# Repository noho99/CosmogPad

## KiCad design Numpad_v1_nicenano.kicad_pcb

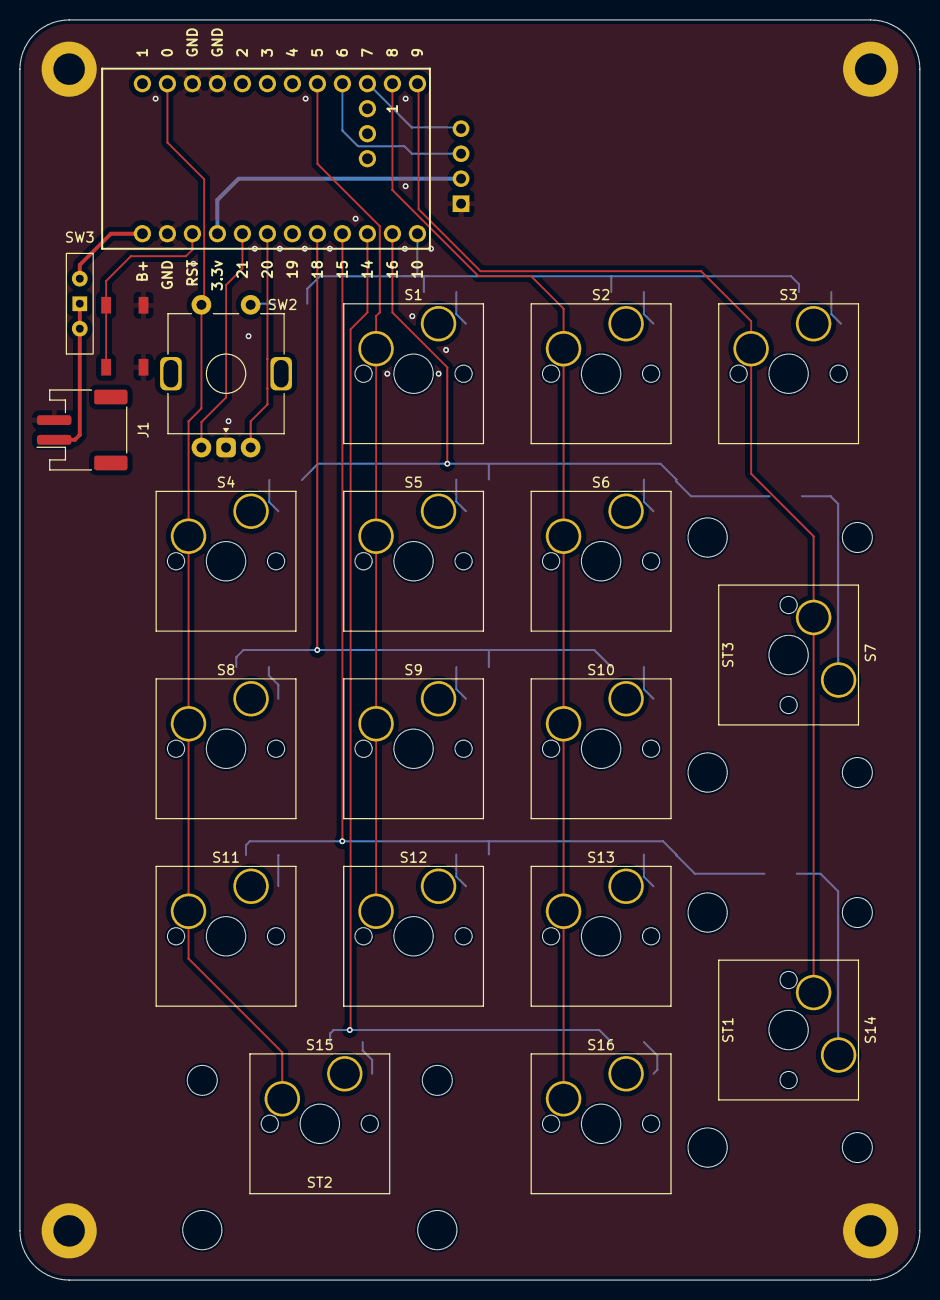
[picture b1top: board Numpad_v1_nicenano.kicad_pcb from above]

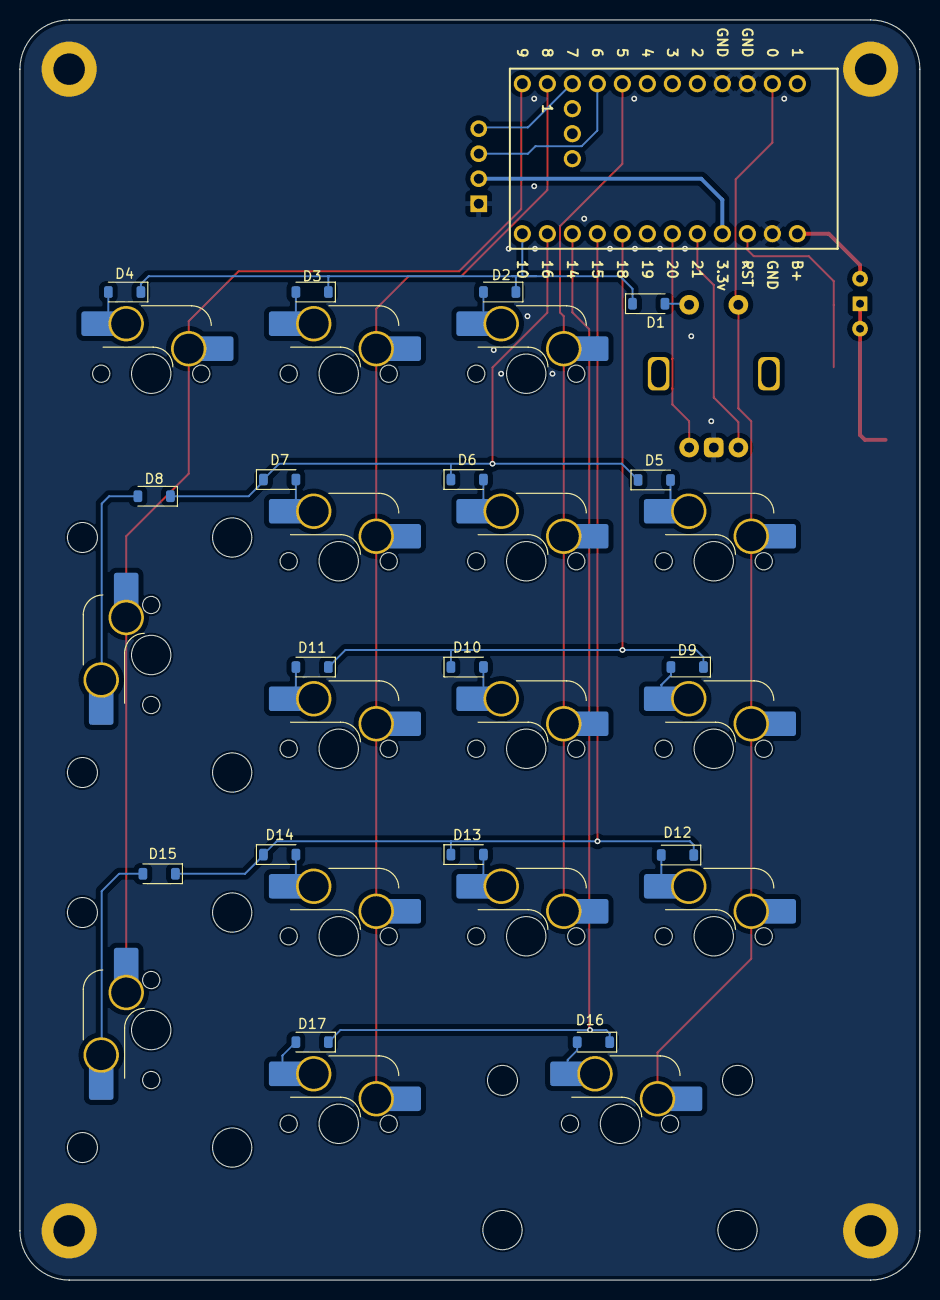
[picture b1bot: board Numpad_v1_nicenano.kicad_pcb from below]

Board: 2 copper layers, 91.4 x 128.0 mm, 46 parts (18 on the bottom side), 35 nets.

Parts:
D1, D2, D3, D4, D5, D6, D7, D8, D9, D10, D11, D12, D13, D14, D15, D16, D17: Diode; D_SOD-123
H1, H2, H3, H4: MountingHole_Pad; MountingHole_3.2mm_M3_DIN965_Pad
J1: Conn_01x02_Socket; JST_PH_S2B-PH-SM4-TB_1x02-1MP_P2.00mm_Horizontal
J2: OLED_128x32
S1, S2, S3, S4, S5, S6, S8, S9, S10, S11, S12, S13, S16: Keyswitch; SW_Hotswap_Kailh_MX_Plated_1.00u
S7, S14, S15: Keyswitch; SW_Hotswap_Kailh_MX_Plated_2.00u
ST1, ST2, ST3: MX_stab_2; Stabilizer_Cherry_MX_2.00u
SW1: SW_DPST_x2; Button_TL3342
SW2: RotaryEncoder_Switch; ROT_Alps_EC11E-Switch
SW3: SW_Wuerth_450301014042; SW_Slide-03_Wuerth-WS-SLTV_10x2.5x6.4_P2.54mm
U1: Nice_Nano_V2

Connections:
3.3V: J2.2 (VCC), U1.21 (3.3v)
3.7V: J1.1, SW3.1 (B), SW3.2 (C)
B+: SW3.3 (A), U1.24 (B+)
Col 1: S4.1, S8.1, S11.1, S15.1, SW2.S2, U1.2 (0)
Col 2: S1.1, S5.1, S9.1, S12.1, U1.8 (5)
Col 3: S2.1, S6.1, S10.1, S13.1, S16.1, U1.11 (8)
Col 4: S3.1, S7.1, S14.1, U1.12 (9)
GND: H1.1, H2.1, H3.1, H4.1, J1.2, J2.1 (GND), SW1.2 (B), SW2.C, U1.3 (GND), U1.4 (GND), U1.23 (GND)
unnamed: D2.2 (A), S1.2
unnamed: D3.2 (A), S2.2
unnamed: D4.2 (A), S3.2
unnamed: D5.2 (A), S4.2
unnamed: D6.2 (A), S5.2
unnamed: D7.2 (A), S6.2
unnamed: D8.2 (A), S7.2
unnamed: D9.2 (A), S8.2
unnamed: D10.2 (A), S9.2
unnamed: D11.2 (A), S10.2
unnamed: D12.2 (A), S11.2
unnamed: D13.2 (A), S12.2
unnamed: D14.2 (A), S13.2
unnamed: D15.2 (A), S14.2
unnamed: D16.2 (A), S15.2
unnamed: D17.2 (A), S16.2
RST: SW1.1 (A), U1.22 (RST)
Rot_A: SW2.A, U1.20 (21)
Rot_B: SW2.B, U1.19 (20)
Rot_S1: D1.2 (A), SW2.S1
Row 1: D1.1 (K), D2.1 (K), D3.1 (K), D4.1 (K), U1.13 (10)
Row 2: D5.1 (K), D6.1 (K), D7.1 (K), D8.1 (K), U1.14 (16)
Row 3: D9.1 (K), D10.1 (K), D11.1 (K), U1.17 (18)
Row 4: D12.1 (K), D13.1 (K), D14.1 (K), D15.1 (K), U1.16 (15)
Row 5: D16.1 (K), D17.1 (K), U1.15 (14)
SCL: J2.3 (SCL), U1.9 (6)
SDA: J2.4 (SDA), U1.10 (7)

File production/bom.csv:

Designator,Footprint,Quantity,Value,LCSC Part #
"D1, D10, D11, D12, D13, D14, D15, D16, D17, D2, D3, D4, D5, D6, D7, D8, D9",D_SOD-123,17,Diode,
J1,JST_PH_S2B-PH-SM4-TB_1x02-1MP_P2.00mm_Horizontal,1,Conn_01x02_Socket,
J2,OLED_128x32,1,OLED_128x32,
"S1, S10, S11, S12, S13, S16, S2, S3, S4, S5, S6, S8, S9",SW_Hotswap_Kailh_MX_Plated_1.00u,13,Keyswitch,
"S14, S15, S7",SW_Hotswap_Kailh_MX_Plated_2.00u,3,Keyswitch,
"ST1, ST2, ST3",Stabilizer_Cherry_MX_2.00u,3,MX_stab_2,
SW1,Button_TL3342,1,SW_DPST_x2,
SW2,ROT_Alps_EC11E-Switch,1,RotaryEncoder_Switch,
SW3,SW_Slide-03_Wuerth-WS-SLTV_10x2.5x6.4_P2.54mm,1,SW_Wuerth_450301014042,
U1,Nice_Nano_V2,1,Nice_Nano_V2,

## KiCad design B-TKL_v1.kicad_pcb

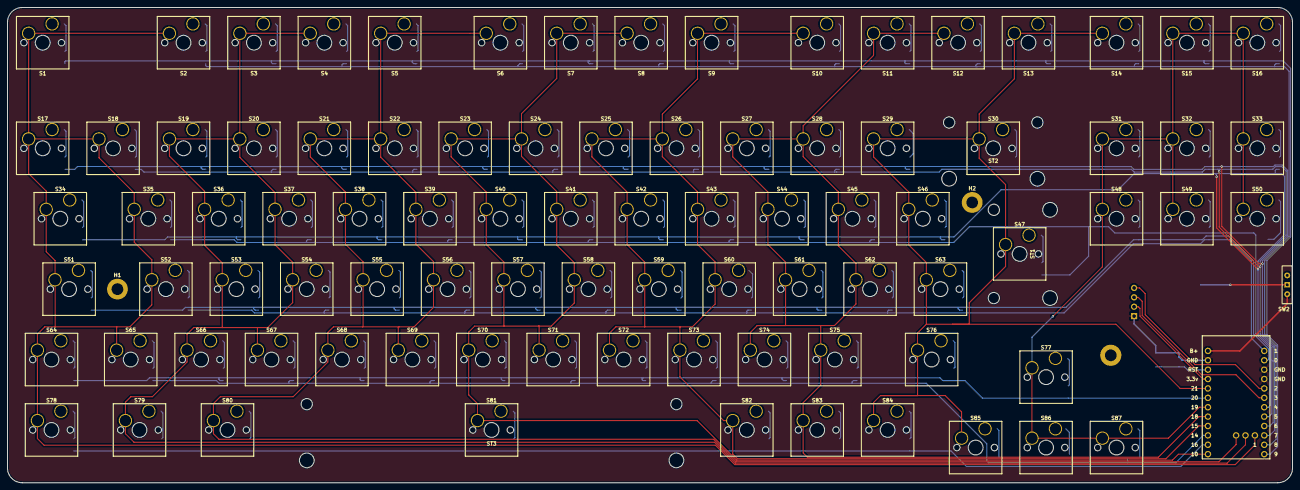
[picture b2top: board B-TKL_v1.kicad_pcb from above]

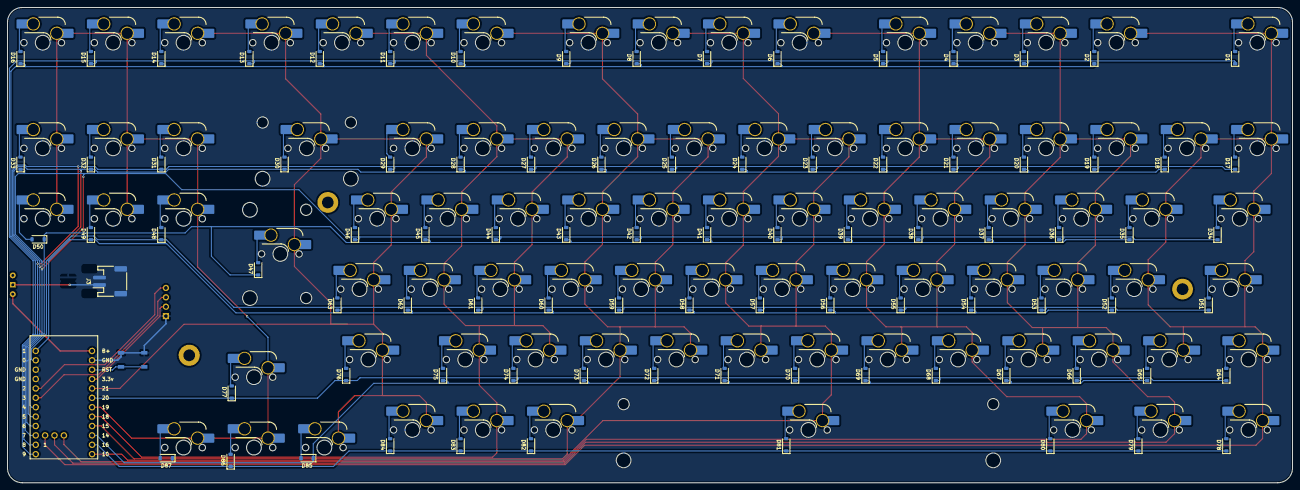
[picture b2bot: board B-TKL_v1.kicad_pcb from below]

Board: 2 copper layers, 347.7 x 128.6 mm, 185 parts (90 on the bottom side), 113 nets.

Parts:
D1, D2, D3, D4, D5, D6, D7, D8, D9, D10, D11, D12, D13, D14, D15, D16, D17, D18, D19, D20, D21, D22, D23, D24, D25, D26, D27, D28, D29, D30, D31, D32, D33, D34, D35, D36, D37, D38, D39, D40, D41, D42, D43, D44, D45, D46, D47, D48, D49, D50, D51, D52, D53, D54, D55, D56, D57, D58, D59, D60, D61, D62, D63, D64, D65, D66, D67, D68, D69, D70, D71, D72, D73, D74, D75, D76, D77, D78, D79, D80, D81, D82, D83, D84, D85, D86, D87: Diode; D_SOD-123
H1, H2: MountingHole; MountingHole_3.2mm_M3_DIN965_Pad
H3: MountingHole; MountingHole_3.2mm_M3_ISO7380_Pad
J1: OLED_128x32
J3: Conn_01x02_Socket; JST_PH_S2B-PH-SM4-TB_1x02-1MP_P2.00mm_Horizontal
S1, S2, S3, S4, S5, S6, S7, S8, S9, S10, S11, S12, S13, S14, S15, S16, S17, S18, S19, S20, S21, S22, S23, S24, S25, S26, S27, S28, S29, S31, S32, S33, S35, S36, S37, S38, S39, S40, S41, S42, S43, S44, S45, S46, S48, S49, S50, S52, S53, S54, S55, S56, S57, S58, S59, S60, S61, S62, S63, S65, S66, S67, S68, S69, S70, S71, S72, S73, S74, S75, S77, S82, S83, S84, S85, S86, S87: Keyswitch; Hotswap_MX_Plated_1.00u
S30: Keyswitch; Hotswap_MX_Plated_2.00u
S34: Keyswitch; Hotswap_MX_Plated_1.50u
S47: Keyswitch; Hotswap_MX_Plated_ISOEnter
S51, S76: Keyswitch; Hotswap_MX_Plated_1.75u
S64, S78, S79, S80: Keyswitch; Hotswap_MX_Plated_1.25u
S81: Keyswitch; Hotswap_MX_Plated_6.25u
ST1, ST2: MX_stab_2; Stabilizer_Cherry_MX_2.00u
ST3: MX_stab_6.25; Stabilizer_MX_6.25u
SW1: SW_DPST_x2; Button_TL3342
SW2: SW_Wuerth_450301014042; SW_Slide-03_Wuerth-WS-SLTV_10x2.5x6.4_P2.54mm
U1: Nice_Nano_V2

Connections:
3.3V: J1.2 (VCC), U1.21 (3.3v)
3.7V: J3.1, SW2.1 (B)
B+: SW2.3 (A), U1.24 (B+)
Col 1: S1.1, S2.1, S17.1, S18.1, S34.1, S35.1, S51.1, S52.1, S64.1, S65.1, S78.1, U1.25 (1)
Col 2: S3.1, S4.1, S19.1, S20.1, S36.1, S37.1, S53.1, S54.1, S66.1, S67.1, S79.1, U1.26 (2)
Col 3: S5.1, S6.1, S21.1, S22.1, S38.1, S39.1, S55.1, S56.1, S68.1, S69.1, S80.1, U1.27 (7)
Col 4: S7.1, S8.1, S23.1, S24.1, S40.1, S41.1, S57.1, S58.1, S70.1, S71.1, S81.1, U1.13 (10)
Col 5: S9.1, S10.1, S25.1, S26.1, S42.1, S43.1, S59.1, S60.1, S72.1, S73.1, S82.1, U1.16 (15)
Col 6: S11.1, S12.1, S27.1, S28.1, S44.1, S45.1, S61.1, S62.1, S74.1, S75.1, S83.1, U1.17 (18)
Col 7: S13.1, S14.1, S29.1, S30.1, S46.1, S47.1, S63.1, S76.1, S84.1, S85.1, U1.20 (21)
Col 8: S15.1, S16.1, S31.1, S32.1, S33.1, S48.1, S49.1, S50.1, S77.1, S86.1, S87.1, U1.18 (19)
GND: J1.1 (GND), J3.2, SW1.2 (B), U1.3 (GND), U1.4 (GND), U1.23 (GND)
unnamed: D1.2 (A), S1.2
unnamed: D2.2 (A), S2.2
unnamed: D3.2 (A), S3.2
unnamed: D4.2 (A), S4.2
unnamed: D5.2 (A), S5.2
unnamed: D6.2 (A), S6.2
unnamed: D7.2 (A), S7.2
unnamed: D8.2 (A), S8.2
unnamed: D9.2 (A), S9.2
unnamed: D10.2 (A), S10.2
unnamed: D11.2 (A), S11.2
unnamed: D12.2 (A), S12.2
unnamed: D13.2 (A), S13.2
unnamed: D14.2 (A), S14.2
unnamed: D15.2 (A), S15.2
unnamed: D16.2 (A), S16.2
unnamed: D17.2 (A), S17.2
unnamed: D18.2 (A), S18.2
unnamed: D19.2 (A), S19.2
unnamed: D20.2 (A), S20.2
unnamed: D21.2 (A), S21.2
unnamed: D22.2 (A), S22.2
unnamed: D23.2 (A), S23.2
unnamed: D24.2 (A), S24.2
unnamed: D25.2 (A), S25.2
unnamed: D26.2 (A), S26.2
unnamed: D27.2 (A), S27.2
unnamed: D28.2 (A), S28.2
unnamed: D29.2 (A), S29.2
unnamed: D30.2 (A), S30.2
unnamed: D31.2 (A), S31.2
unnamed: D32.2 (A), S32.2
unnamed: D33.2 (A), S33.2
unnamed: D34.2 (A), S34.2
unnamed: D35.2 (A), S35.2
unnamed: D36.2 (A), S36.2
unnamed: D37.2 (A), S37.2
unnamed: D38.2 (A), S38.2
unnamed: D39.2 (A), S39.2
unnamed: D40.2 (A), S40.2
unnamed: D41.2 (A), S41.2
unnamed: D42.2 (A), S42.2
unnamed: D43.2 (A), S43.2
unnamed: D44.2 (A), S44.2
unnamed: D45.2 (A), S45.2
unnamed: D46.2 (A), S46.2
unnamed: D47.2 (A), S47.2
unnamed: D48.2 (A), S48.2
unnamed: D49.2 (A), S49.2
unnamed: D50.2 (A), S50.2
unnamed: D51.2 (A), S51.2
unnamed: D52.2 (A), S52.2
unnamed: D53.2 (A), S53.2
unnamed: D54.2 (A), S54.2
unnamed: D55.2 (A), S55.2
unnamed: D56.2 (A), S56.2
unnamed: D57.2 (A), S57.2
unnamed: D58.2 (A), S58.2
unnamed: D59.2 (A), S59.2
unnamed: D60.2 (A), S60.2
unnamed: D61.2 (A), S61.2
unnamed: D62.2 (A), S62.2
unnamed: D63.2 (A), S63.2
unnamed: D64.2 (A), S64.2
unnamed: D65.2 (A), S65.2
unnamed: D66.2 (A), S66.2
unnamed: D67.2 (A), S67.2
unnamed: D68.2 (A), S68.2
unnamed: D69.2 (A), S69.2
unnamed: D70.2 (A), S70.2
unnamed: D71.2 (A), S71.2
unnamed: D72.2 (A), S72.2
unnamed: D73.2 (A), S73.2
unnamed: D74.2 (A), S74.2
unnamed: D75.2 (A), S75.2
unnamed: D76.2 (A), S76.2
unnamed: D77.2 (A), S77.2
unnamed: D78.2 (A), S78.2
unnamed: D79.2 (A), S79.2
unnamed: D80.2 (A), S80.2
unnamed: D81.2 (A), S81.2
unnamed: D82.2 (A), S82.2
unnamed: D83.2 (A), S83.2
unnamed: D84.2 (A), S84.2
unnamed: D85.2 (A), S85.2
unnamed: D86.2 (A), S86.2
unnamed: D87.2 (A), S87.2
RST: SW1.1 (A), U1.22 (RST)
Row 1: D1.1 (K), D3.1 (K), D5.1 (K), D7.1 (K), D9.1 (K), D11.1 (K), D13.1 (K), D15.1 (K), U1.12 (9)
Row 2: D2.1 (K), D4.1 (K), D6.1 (K), D8.1 (K), D10.1 (K), D12.1 (K), D14.1 (K), D16.1 (K), U1.11 (8)
Row 3: D17.1 (K), D19.1 (K), D21.1 (K), D23.1 (K), D25.1 (K), D27.1 (K), D29.1 (K), D31.1 (K), U1.10 (7)
Row 4: D18.1 (K), D20.1 (K), D22.1 (K), D24.1 (K), D26.1 (K), D28.1 (K), D30.1 (K), D32.1 (K), U1.9 (6)
Row 5: D33.1 (K), D34.1 (K), D36.1 (K), D38.1 (K), D40.1 (K), D42.1 (K), D44.1 (K), D46.1 (K), U1.8 (5)
Row 6: D35.1 (K), D37.1 (K), D39.1 (K), D41.1 (K), D43.1 (K), D45.1 (K), D47.1 (K), D50.1 (K), U1.7 (4)
Row 7: D48.1 (K), D51.1 (K), D53.1 (K), D55.1 (K), D57.1 (K), D59.1 (K), D61.1 (K), D63.1 (K), U1.2 (0)
Row 8: D49.1 (K), D52.1 (K), D54.1 (K), D56.1 (K), D58.1 (K), D60.1 (K), D62.1 (K), U1.1
Row 9: D64.1 (K), D66.1 (K), D68.1 (K), D70.1 (K), D72.1 (K), D74.1 (K), D76.1 (K), D77.1 (K), U1.19 (20)
Row 10: D65.1 (K), D67.1 (K), D69.1 (K), D71.1 (K), D73.1 (K), D75.1 (K), D85.1 (K), D87.1 (K), U1.15 (14)
Row 11: D78.1 (K), D79.1 (K), D80.1 (K), D81.1 (K), D82.1 (K), D83.1 (K), D84.1 (K), D86.1 (K), U1.14 (16)
SCL: J1.3 (SCL), U1.6 (3)
SDA: J1.4 (SDA), U1.5 (2)
